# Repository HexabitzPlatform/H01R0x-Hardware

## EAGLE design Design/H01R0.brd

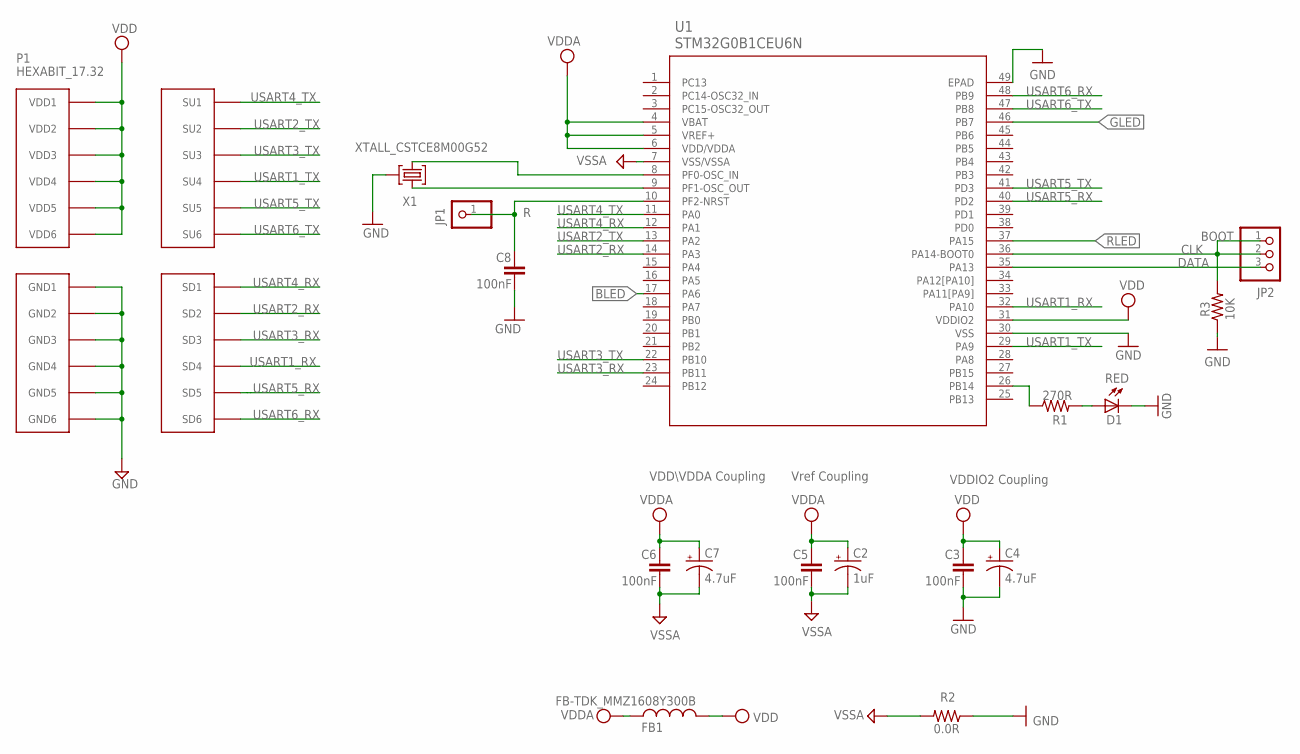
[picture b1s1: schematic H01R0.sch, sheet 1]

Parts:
C2: 1uF; C-0805-POL
C3, C5, C6, C8: 100nF; C-0603
C4, C7: 4.7uF; C-0805-POL
D1: RED; VLMS1300-GS08; MPN VLMS1300-GS08
FB1: FB-TDK_MMZ1608Y300B; FB-0603; MPN MMZ1608Y300B
JP1: R; 1X01
JP2: PINHD-1X3; 1X03
P1: HEXABIT_17.32
R1: 270R; R-0603
R2: 0.0R; R-0603; MPN RC0603JR-070RL
R3: 10K; R-0603
U1: STM32G0B1CEU6N; HEXABITZ_ICS_QFN_B1CEU6_STM-L
X1: XTALL_CSTCE8M00G52

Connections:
BLED: U1.17 (PA6); also elsewhere on the board
CLK: JP2.1, JP2.2, R3.2, U1.36 (PA14-BOOT0)
DATA: JP2.3, U1.35 (PA13)
GLED: U1.46 (PB7); also elsewhere on the board
GND: C3.2, C4.2 (-), C8.2, D1.C, P1.PAD_PD7 (GND1), P1.PAD_PD8 (GND2), P1.PAD_PD9 (GND3), P1.PAD_PD10 (GND4), P1.PAD_PD11 (GND5), P1.PAD_PD12 (GND6), R2.1, R3.1, U1.30 (VSS), U1.49 (EPAD), X1.P$2 (2); also elsewhere on the board
unnamed: D1.A, R1.2
unnamed: C8.1, JP1.1, U1.10 (PF2-NRST)
unnamed: U1.9 (PF1-OSC_OUT), X1.P$1 (1)
unnamed: U1.8 (PF0-OSC_IN), X1.P$3 (3)
unnamed: R1.1, U1.26 (PB14)
RLED: U1.37 (PA15); also elsewhere on the board
USART1_RX: P1.PAD_PD4 (SD4), U1.32 (PA10)
USART1_TX: P1.PAD_PU4 (SU4), U1.29 (PA9)
USART2_RX: P1.PAD_PD2 (SD2), U1.14 (PA3)
USART2_TX: P1.PAD_PU2 (SU2), U1.13 (PA2)
USART3_RX: P1.PAD_PD3 (SD3), U1.23 (PB11)
USART3_TX: P1.PAD_PU3 (SU3), U1.22 (PB10)
USART4_RX: P1.PAD_PD1 (SD1), U1.12 (PA1)
USART4_TX: P1.PAD_PU1 (SU1), U1.11 (PA0)
USART5_RX: P1.PAD_PD5 (SD5), U1.40 (PD2)
USART5_TX: P1.PAD_PU5 (SU5), U1.41 (PD3)
USART6_RX: P1.PAD_PD6 (SD6), U1.48 (PB9)
USART6_TX: P1.PAD_PU6 (SU6), U1.47 (PB8)
VDD: C3.1, C4.1 (+), FB1.2, P1.PAD_PU7 (VDD1), P1.PAD_PU8 (VDD2), P1.PAD_PU9 (VDD3), P1.PAD_PU10 (VDD4), P1.PAD_PU11 (VDD5), P1.PAD_PU12 (VDD6), U1.31 (VDDIO2); also elsewhere on the board
VDDA: C2.1 (+), C5.1, C6.1, C7.1 (+), FB1.1, U1.4 (VBAT), U1.5 (VREF+), U1.6 (VDD/VDDA)
VSSA: C2.2 (-), C5.2, C6.2, C7.2 (-), R2.2, U1.7 (VSS/VSSA)

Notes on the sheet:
Vref Coupling
VDDIO2 Coupling
VDD\VDDA Coupling
BOOT

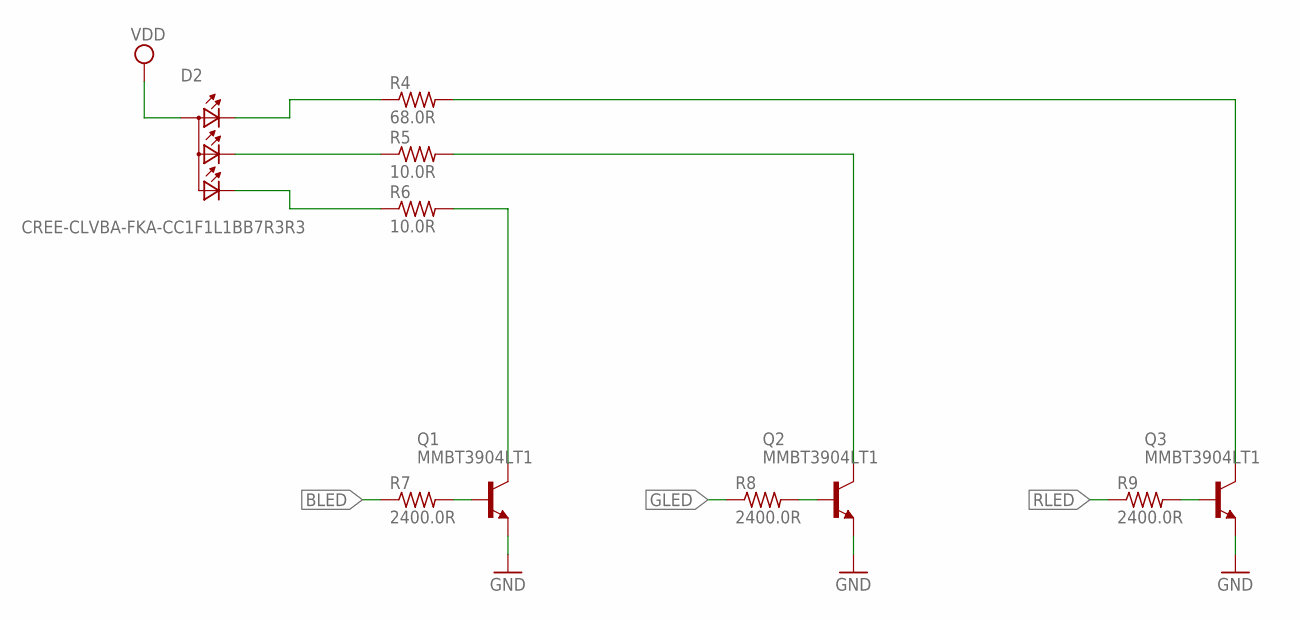
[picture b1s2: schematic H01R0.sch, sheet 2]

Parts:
D2: CREE-CLVBA-FKA-CC1F1L1BB7R3R3; PCB-1023943-1; MPN CLVBA-FKA-CC1F1L1BB7R3R3
Q1: MMBT3904LT1; VOLTAGE_RATING_DC 40.0V; MPN MMBT3904LT1G
Q2, Q3: MMBT3904LT1; VOLTAGE_RATING_DC 40.0V
R4: 68.0R; R-0603; TOLERANCE 1%; MPN CRCW060368R0FKEA
R5, R6: 10.0R; R-0603; TOLERANCE 1%; MPN CRCW060310R0FKEB
R7, R8, R9: 2400.0R; R-0603; TOLERANCE 5%; MPN CRCW06032K40JNEA

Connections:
BLED: R7.1; also elsewhere on the board
GLED: R8.1; also elsewhere on the board
GND: Q1.2 (E), Q2.2 (E), Q3.2 (E); also elsewhere on the board
unnamed: D2.P$1 (CRED), R4.1
unnamed: D2.P$4 (CGREEN), R5.1
unnamed: D2.P$3 (CBLUE), R6.1
unnamed: Q1.3 (C), R6.2
unnamed: Q2.3 (C), R5.2
unnamed: Q3.3 (C), R4.2
unnamed: Q1.1 (B), R7.2
unnamed: Q2.1 (B), R8.2
unnamed: Q3.1 (B), R9.2
RLED: R9.1; also elsewhere on the board
VDD: D2.P$2 (A2); also elsewhere on the board

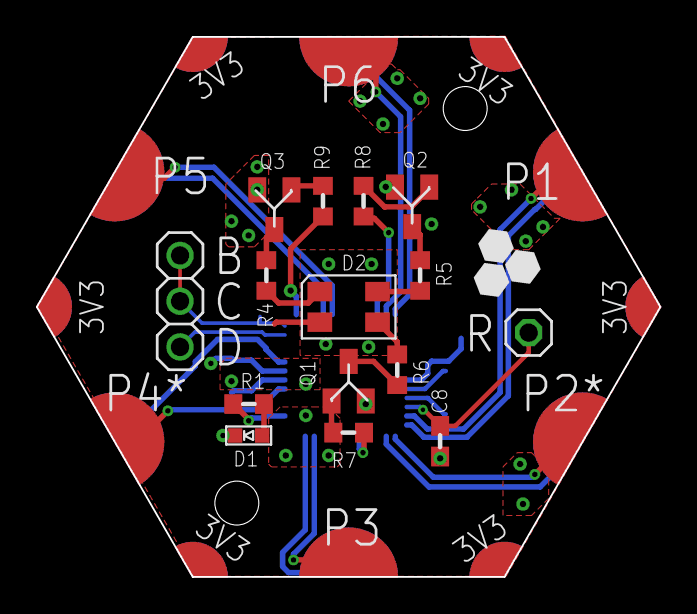
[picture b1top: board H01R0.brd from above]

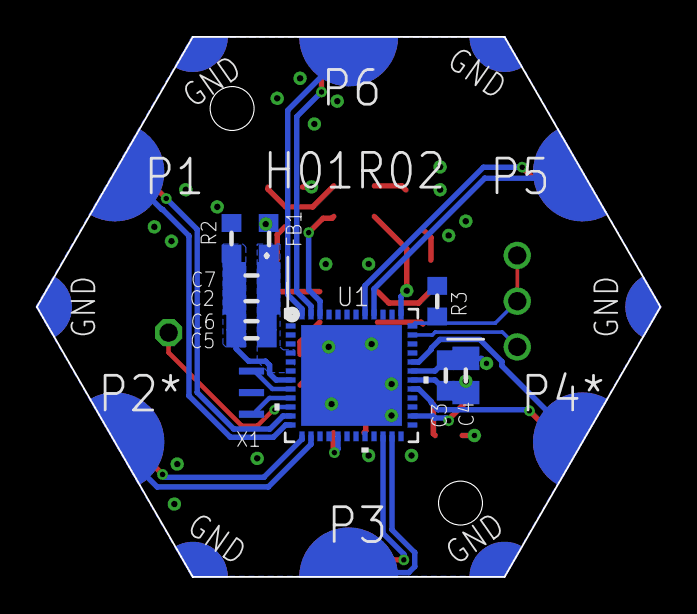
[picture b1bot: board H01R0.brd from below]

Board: 2 copper layers, 34.6 x 30.0 mm, 27 parts (11 on the bottom side), 35 nets.

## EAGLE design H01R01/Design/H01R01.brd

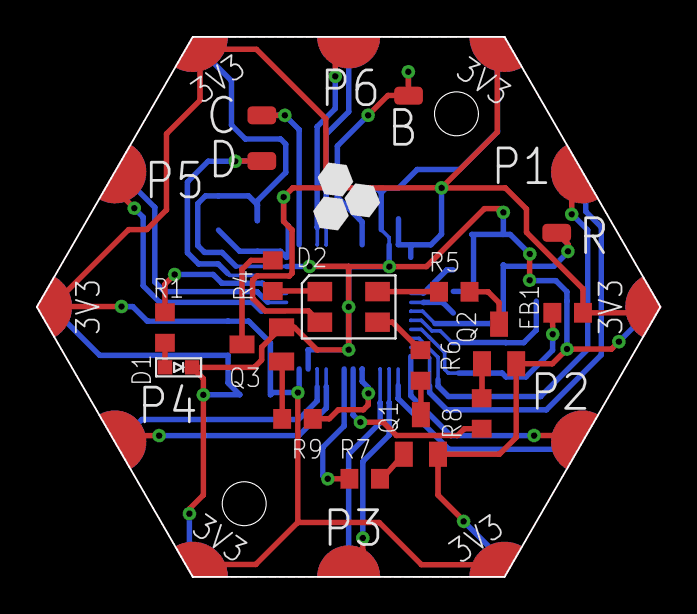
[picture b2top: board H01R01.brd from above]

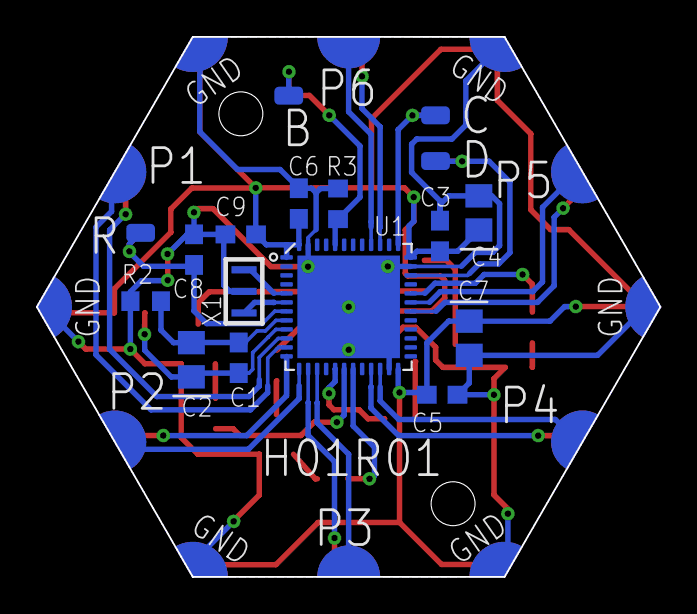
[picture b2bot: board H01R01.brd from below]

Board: 2 copper layers, 34.6 x 30.0 mm, 31 parts (13 on the bottom side), 36 nets.

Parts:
B: PAD1
C: PAD1
C1: 10nF; C-0603
C2: 1.00uF; C-0805-POL
C3, C5, C6, C8, C9: 100nF; C-0603
C4, C7: 4.7uF; C-0805-POL
D: PAD1
D1: VLMS1300-GS08
D2: CREE-CLVBA-FKA-CC1F1L1BB7R3R3; PCB-1023943-1
FB1: FB-TDK_MMZ1608Y300B
P1: HEXABIT_17.32
Q1, Q2, Q3: MMBT3904LT1
R: PAD1
R1: 270.0R; R-0603
R2: 0.0R; R-0603
R3: 10.0K; R-0603
R4: 68.0R; R-0603
R5, R6: 10.0R; R-0603
R7, R8, R9: 2400.0R; R-0603
U1: STM32F091CBU6
X1: XTALL_CSTCE8M00G52

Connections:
B1: B.P$1, B.P$2, R3.2, U1.P$44
BLED: R7.1, U1.P$19
GLED: R8.1, U1.P$18
GND: C3.2, C4.2, C5.2, C6.2, C7.2, C8.2, C9.2, D1.C, P1.PAD_PD7, P1.PAD_PD8, P1.PAD_PD9, P1.PAD_PD10, P1.PAD_PD11, P1.PAD_PD12, Q1.2, Q2.2, Q3.2, R2.1, R3.1, U1.EP, U1.P$23, U1.P$35, U1.P$47, X1.P$2
unnamed: D2.P$1, R4.1
unnamed: D2.P$4, R5.1
unnamed: R1.2, U1.P$32
unnamed: D1.A, R1.1
unnamed: U1.P$5, X1.P$1
unnamed: U1.P$6, X1.P$3
unnamed: D.P$1, D.P$2, U1.P$34
unnamed: D2.P$3, R6.1
unnamed: C.P$1, C.P$2, U1.P$37
unnamed: Q1.3, R6.2
unnamed: Q2.3, R5.2
unnamed: Q3.3, R4.2
unnamed: Q1.1, R7.2
unnamed: Q2.1, R8.2
unnamed: Q3.1, R9.2
R1: C8.1, R.P$1, R.P$2, U1.P$7
RLED: R9.1, U1.P$17
USART1_RX: P1.PAD_PD5, U1.P$31
USART1_TX: P1.PAD_PU5, U1.P$30
USART2_RX: P1.PAD_PD2, U1.P$13
USART2_TX: P1.PAD_PU2, U1.P$12
USART3_RX: P1.PAD_PD4, U1.P$22
USART3_TX: P1.PAD_PU4, U1.P$21
USART4_RX: P1.PAD_PD1, U1.P$11
USART4_TX: P1.PAD_PU1, U1.P$10
USART5_RX: P1.PAD_PD6, U1.P$40
USART5_TX: P1.PAD_PU6, U1.P$39
USART6_RX: P1.PAD_PD3, U1.P$15
USART6_TX: P1.PAD_PU3, U1.P$14
VDD: C3.1, C4.1, C5.1, C6.1, C7.1, C9.1, D2.P$2, FB1.2, P1.PAD_PU7, P1.PAD_PU8, P1.PAD_PU9, P1.PAD_PU10, P1.PAD_PU11, P1.PAD_PU12, U1.P$1, U1.P$24, U1.P$36, U1.P$48
VDDA: C1.1, C2.1, FB1.1, U1.P$9
VSSA: C1.2, C2.2, R2.2, U1.P$8

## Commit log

2019-05-23 First release rev 0
2019-05-23 Revert "First release rev 0"
    This reverts commit 8fc064089e4cd6e668830f0ecfbded621433f5e1.
2019-05-23 First release rev 1
    Moved mounting holes
2021-04-28 - Changed Hole size to the standarad m2 (2.44mm).. - Regenerated output files..
2022-08-16 Changing MCU to STM32G0
2023-02-15 -Correcting some documentaion issues
2024-01-02 -Standarize the files and folders
2024-02-13 -Improving the Layout Design

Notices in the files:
parts and their libraries:
HEXABITZ_ICs: COPYRIGHT: Copyright (C) 2022 Ultra Librarian. All rights reserved.
